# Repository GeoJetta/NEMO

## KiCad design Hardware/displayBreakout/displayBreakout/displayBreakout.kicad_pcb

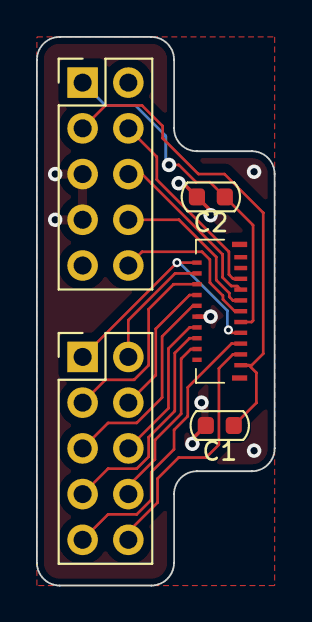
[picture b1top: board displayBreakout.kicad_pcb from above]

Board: 2 copper layers, 13.2 x 30.5 mm, 5 parts (0 on the bottom side), 17 nets.

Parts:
C1, C2: 1uF; C_0603_1608Metric
J1: 503566-2102; 5035662102
J2, J3: Conn_02x05_Odd_Even; PinHeader_2x05_P2.54mm_Vertical

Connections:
+3.3V: C2.1, J1.9 (VDD1), J2.1
+5V: C1.1, J1.1 (VDD2), J2.3
/B0: J1.17 (B0), J2.4
/B1: J1.18 (B1), J3.2
/BCK: J1.12 (BCK), J3.5
/BSP: J1.11 (BSP), J2.10
/G0: J1.15 (G0), J2.6
/G1: J1.16 (G1), J3.3
/GCK: J1.4 (GCK), J3.8
/GEN: J1.5 (GEN), J3.9
/GSP: J1.3 (GSP), J3.10
/INTB: J1.6 (INTB), J3.7
/R0: J1.13 (R0), J2.8
/R1: J1.14 (R1), J3.4
/VA: J1.8 (VA), J3.6
/VCOM: J1.7 (VB), J1.20 (VCOM), J3.1
GND: C1.2, C2.2, J1.10 (VSS), J2.5, J2.7

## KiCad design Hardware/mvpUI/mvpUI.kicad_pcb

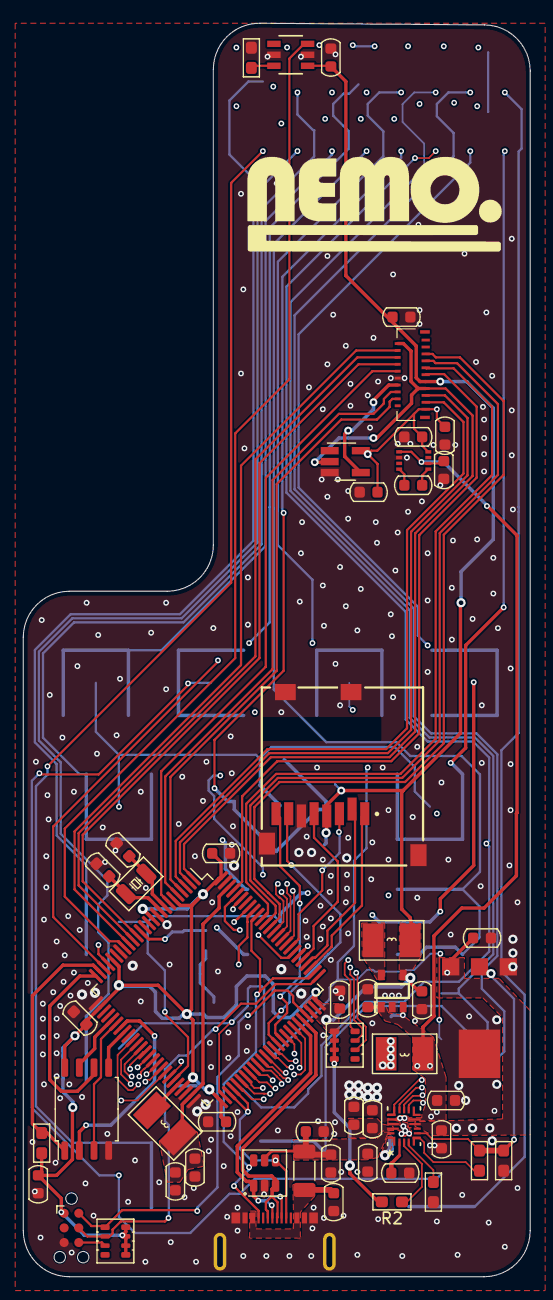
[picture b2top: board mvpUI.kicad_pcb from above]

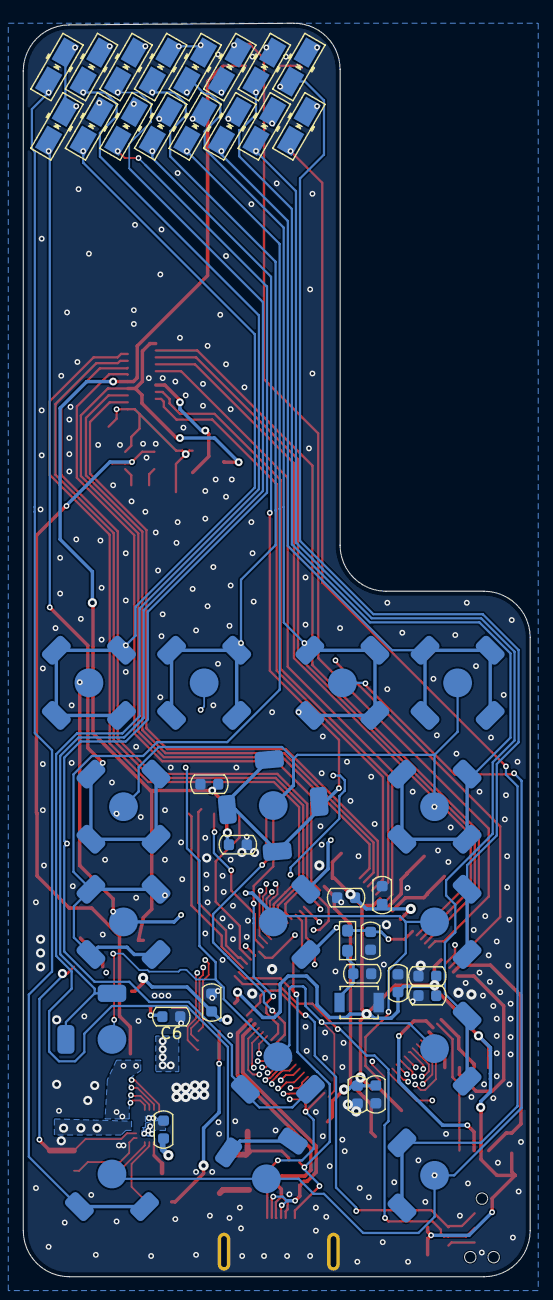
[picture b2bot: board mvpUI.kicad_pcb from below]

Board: 4 copper layers, 44.0 x 108.8 mm, 102 parts (48 on the bottom side), 87 nets.

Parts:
C1, C16, C20, C21, C36, C44, C51: 10uF; C_0603_1608Metric
C2, C32, C37, C38, C45, C46, C47, C49, C52, C53: 100nF; C_0603_1608Metric
C3, C4, C5, C39, C48, C50: 1uF; C_0603_1608Metric
C6, C15, C18, C35, C40: 0.1uF; C_0603_1608Metric
C13: 10pF; C_0603_1608Metric
C14: 22nF; C_0603_1608Metric
C17, C33, C43: 4.7uF; C_0603_1608Metric
C19: 22uF; C_0603_1608Metric
C29, C30: 3.9pF; C_0603_1608Metric
C31: 10nF; C_0603_1608Metric
C34: 100nF X7R; C_0603_1608Metric
C41: 47nF; C_0603_1608Metric
C42: 20uF; C_0603_1608Metric
C54, C55: 2.2uF; C_0603_1608Metric
D1, D2, D4, D5, D6, D7, D8, D9, D10, D11, D12, D13, D14, D15, D16, D17: D; D_MicroMELF_Handsoldering
D3: USBLC6-4SC6; SOT-23-6
F1: Polyfuse; L_1206_3216Metric_Pad1.22x1.90mm_HandSolder
IC1: XC9265B331MR-G; SOT95P280X130-5N
J1: Conn_ARM_SWD_TagConnect_TC2030-NL; Tag-Connect_TC2030-IDC-NL_2x03_P1.27mm_Vertical
J2: 54-00305; CX90BW-16P
J3: MEM2061-01-188-00-A_REVA; GCT_MEM2061-01-188-00-A_REVA
J4: 503566-2102; 5035662102
L2: 10uH; L_Taiyo-Yuden_NR-30xx_HandSoldering
L3: 2.2uH; L_Taiyo-Yuden_NR-30xx_HandSoldering
L4: 1uH; L_Taiyo-Yuden_NR-30xx_HandSoldering
R1, R2: 10k; R_0603_1608Metric_Pad1.05x0.95mm_HandSolder
R3: 1K; R_0603_1608Metric_Pad1.05x0.95mm_HandSolder
R4: 5.3k; R_0603_1608Metric_Pad1.05x0.95mm_HandSolder
R5: 31.1k; R_0603_1608Metric_Pad1.05x0.95mm_HandSolder
R6: 5k; R_0603_1608Metric_Pad1.05x0.95mm_HandSolder
R9: 910; R_0603_1608Metric_Pad1.05x0.95mm_HandSolder
RN1: 4x10k; R_Array_Convex_4x0603
RN2: 4x47; R_Array_Convex_4x0603
SW1: SW_Push; SW_SPST_B3U-1000P
SW3, SW4, SW5, SW6, SW15, SW16, SW17, SW18: snap_dome; snap dome_1
SW7, SW8, SW9, SW10, SW11, SW12, SW13, SW14: snap_dome; snap dome_2
U1: MX25R3235FM2xx0; SOP-8_5.28x5.23mm_P1.27mm
U2: 00-9155-003-00 3 Pin Spring Connector
U3: PTMAG5328A1DQDBVR; SOT23_DBV_TEX-M
U4: 74LVC1GU04DRL; SOT-23-5_HandSoldering
U5: BQ25622ERYKR; WQFN-HR18_RYK_TEX
U6: S-882150APH
U8: STM32U585VIT6Q; LQFP-100_14x14mm_P0.5mm
Y2: Crystal; Crystal_SMD_3215-2Pin_3.2x1.5mm

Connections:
+3.3V: C1.1, C2.1, C3.1, C5.1, C19.1, C34.2, C36.1, C37.1, C38.1, C45.1, C46.1, C47.1, C48.1, C49.1, C50.1, C51.1, C52.1, C53.1, IC1.4 (VOUT), J1.1 (VCC), J3.4 (VDD), J4.9 (VDD1), L2.2, R1.2, R2.2, RN1.5 (R4.2), RN1.6 (R3.2), RN1.7 (R2.2), RN1.8 (R1.2), RN2.5 (R4.2), RN2.6 (R3.2), RN2.7 (R2.2), RN2.8 (R1.2), U1.8 (VCC), U3.4 (VCC), U8.6 (VBAT), U8.11 (VDD), U8.21 (VDDA), U8.27 (VDD), U8.47 (VDDSMPS), U8.51 (VDD), U8.73 (VDDUSB), U8.75 (VDD), U8.100 (VDD)
+5V: C4.1, C21.1, C35.1, J4.1 (VDD2), U4.5 (VCC), U6.4 (VOUT)
/Connectors/B0: J4.17 (B0), U8.88 (PD7)
/Connectors/B1: J4.18 (B1), U8.17 (PC2)
/Connectors/BCK: J4.12 (BCK), U8.7 (PC13)
/Connectors/BSP: J4.11 (BSP), U8.97 (PE0)
/Connectors/CC1: D3.6 (L4), J2.A5 (CC1), U8.77 (PA15), U8.91 (PB5)
/Connectors/CC2: D3.4 (L3), J2.B5 (CC2), U8.53 (PB14), U8.54 (PB15)
/Connectors/D+: D3.3 (L2), J2.A6 (DP1), J2.B6 (DP2), U8.71 (PA12)
/Connectors/D-: D3.1 (L1), J2.A7 (DN1), J2.B7 (DN2), U8.70 (PA11)
/Connectors/G0: J4.15 (G0), U8.89 (PB3)
/Connectors/G1: J4.16 (G1), U8.16 (PC1)
/Connectors/GCK: J4.4 (GCK), U8.4 (PE5)
/Connectors/GEN: J4.5 (GEN), U8.2 (PE3)
/Connectors/GSP: J4.3 (GSP), U8.3 (PE4)
/Connectors/INTB: J4.6 (INTB), U8.5 (PE6)
/Connectors/R0: J4.13 (R0), U8.90 (PB4)
/Connectors/R1: J4.14 (R1), U8.15 (PC0)
/Connectors/TEMP: R4.2, R5.2, U2.2 (TEMP), U5.6 (TS)
/Connectors/V+: C15.1, C44.1, U2.3 (+), U5.8 (BAT)
/Connectors/VA: J4.8 (VA), U4.4
/Connectors/VBUS: C32.2, C33.2, C39.1, D3.5 (VP), F1.1, U5.18 (VBUS)
/Connectors/VBUS_RAW: C31.1, F1.2, J2.A4_B9 (VBUS_1), J2.B4_A9 (VBUS_2)
/Connectors/VCOM: J4.7 (VB), J4.20 (VCOM), U4.2, U8.1 (PE2)
/MCU/INT: RN1.4 (R4.1), U5.11 (*INT), U8.96 (PB9)
/MCU/KEYPAD.C0: D6.1 (K), D7.1 (K), D8.1 (K), D9.1 (K), U8.81 (PD0)
/MCU/KEYPAD.C1: D10.1 (K), D11.1 (K), D12.1 (K), D13.1 (K), U8.82 (PD1)
/MCU/KEYPAD.C2: D14.1 (K), D15.1 (K), D16.1 (K), D17.1 (K), U8.23 (PA1)
/MCU/KEYPAD.C3: D1.1 (K), D2.1 (K), D4.1 (K), D5.1 (K), U8.22 (PA0)
/MCU/KEYPAD.R0: SW12.1 (+), SW13.1 (+), SW14.1 (+), SW15.1 (+), U8.43 (PE15)
/MCU/KEYPAD.R1: SW9.1 (+), SW10.1 (+), SW11.1 (+), SW16.1 (+), U8.52 (PB13)
/MCU/KEYPAD.R2: SW6.1 (+), SW7.1 (+), SW8.1 (+), SW17.1 (+), U8.45 (PB11)
/MCU/KEYPAD.R3: SW3.1 (+), SW4.1 (+), SW5.1 (+), SW18.1 (+), U8.44 (PB10)
/MCU/LSE_IN: C29.1, U8.8 (PC14), Y2.1
/MCU/LSE_OUT: C30.1, U8.9 (PC15), Y2.2
/MCU/MAG1_OUT: U3.6 (OUT), U8.18 (PC3)
/MCU/QSPI_102: U1.3 (~WP/SIO2), U8.31 (PA7)
/MCU/QSPI_CLK: U1.6 (SCLK), U8.25 (PA3)
/MCU/QSPI_IO0: U1.5 (SI/SIO0), U8.33 (PB1)
/MCU/QSPI_IO1: U1.2 (SO/SIO1), U8.32 (PB0)
/MCU/QSPI_IO3: U1.7 (~RESET/SIO3), U8.30 (PA6)
/MCU/QSPI_NCS: R1.1, U1.1 (~CS), U8.24 (PA2)
/MCU/SCL: RN1.2 (R2.1), U5.13 (SCL), U8.92 (PB6)
/MCU/SDA: RN1.3 (R3.1), U5.12 (SDA), U8.93 (PB7)
/MCU/SD_CLK: J3.5 (CLK), U8.80 (PC12)
/MCU/SD_CMD: J3.3 (CMD), U8.83 (PD2)
/MCU/SD_IO0: J3.7 (DAT0), U8.65 (PC8)
/MCU/SD_IO1: J3.8 (DAT1), U8.66 (PC9)
/MCU/SD_IO2: J3.1 (DAT2), U8.78 (PC10)
/MCU/SD_IO3: J3.2 (CD/DAT3), U8.79 (PC11)
/MCU/SWCLK: J1.4 (SWCLK), RN2.2 (R2.1), U8.76 (PA14)
/MCU/SWDIO: J1.2 (SWDIO), RN2.1 (R1.1), U8.72 (PA13)
/MCU/SWO: J1.6 (SWO), RN2.3 (R3.1)
/MCU/VDD11C: C54.1, C55.1, L3.1, U8.49 (VDD11), U8.98 (VDD11)
/MCU/VLXS: L3.2, U8.46 (VLXSMPS)
/MCU/~CE: U5.14 (CE), U8.95 (PB8)
GND: C1.2, C2.2, C3.2, C4.2, C5.2, C6.1, C13.1, C14.1, C15.2, C16.2, C17.2, C19.2, C20.2, C21.2, C29.2, C30.2, C31.2, C32.1, C33.1, C34.1, C35.2, C36.2, C37.2, C38.2, C39.2, C40.2, C42.2, C43.2, C44.2, C45.2, C46.2, C47.2, C48.2, C49.2, C50.2, C51.2, C52.2, C53.2, C54.2, C55.2, D3.2 (VN), IC1.2 (GND), J1.5 (GND), J2.A1_B12 (GND_1), J2.B1_A12 (GND_2), J2.S1 (SHIELD), J2.S2 (SHIELD__1), J2.S3 (SHIELD__2), J2.S4 (SHIELD__3), J3.6 (VSS), J3.9 (CD1), J3.10 (CD2), J3.11 (GND), J3.12 (GND__1), J4.10 (VSS), R5.1, R6.2, R9.1, SW1.1, U1.4 (GND), U2.1 (GND), U2.4 (SHIELD), U3.2 (GND), U3.5 (TEST2), U4.3 (GND), U5.15 (GND), U6.6 (GND), U8.10 (VSS), U8.19 (VSSA), U8.26 (VSS), U8.48 (VSSSMPS), U8.50 (VSS), U8.74 (VSS), U8.99 (VSS)
unnamed: C13.2, R3.1, SW1.2
unnamed: D1.2 (A), SW18.2 (-)
unnamed: D2.2 (A), SW17.2 (-)
unnamed: D4.2 (A), SW16.2 (-)
unnamed: D5.2 (A), SW15.2 (-)
unnamed: D6.2 (A), SW3.2 (-)
unnamed: D7.2 (A), SW6.2 (-)
unnamed: D8.2 (A), SW9.2 (-)
unnamed: D9.2 (A), SW12.2 (-)
unnamed: D10.2 (A), SW4.2 (-)
unnamed: D11.2 (A), SW7.2 (-)
unnamed: D12.2 (A), SW10.2 (-)
unnamed: D13.2 (A), SW13.2 (-)
unnamed: D14.2 (A), SW5.2 (-)
unnamed: D15.2 (A), SW8.2 (-)
unnamed: D16.2 (A), SW11.2 (-)
unnamed: D17.2 (A), SW14.2 (-)
unnamed: C6.2, C16.1, C17.1, C42.1, IC1.1 (VIN), IC1.3 (CE), L4.1, U5.9 (SYS), U6.2 (VIN), U6.5 (ON/OFF)
unnamed: IC1.5 (LX), L2.1
unnamed: R6.1, U3.3 (ADJ)
unnamed: R2.1, U5.3 (*PG)
unnamed: C41.1, U5.1 (BTST)
unnamed: R9.2, U5.4 (ILIM)
unnamed: C20.1, C40.1, U5.17 (PMID)
unnamed: C43.1, U5.2 (REGN)
unnamed: C41.2, L4.2, U5.16 (SW)
unnamed: R4.1, U5.5 (TS_BIAS)
unnamed: C18.1, U6.1 (C+)
unnamed: C18.2, U6.8 (C-)
unnamed: C14.2, R3.2, U8.14 (NRST)

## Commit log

2023-10-16 Initial File Migration
2023-10-20 Getting there...
    Just need logic and power planes for the most part (and verify everything once more)
2023-10-22 Getting there part ii
    Started power planes, most of keyboard wired together
2023-10-22 T-2 or 3ish
    Just keypad, decaps, and a checkover left!
2023-10-25 Ready to Review
2023-11-02 Fixed Obvious Dumb
2023-11-12 Production!
    Forgot to commit the final, lets hope this works. Also start on software using Slint. Prototype in Plasticity on a free trial to test.
2023-11-13 Display Driver work
2023-11-13 More Display Docs Updates
2023-11-13 Too many files
2023-11-20 Display breakout PCB
2023-11-20 Framerate estimation
2023-11-28 Lots of experimenting and random stuff
2023-12-28 VHDL Start
2023-12-28 VHDL
2024-01-02 new attempt
2024-01-02 name
